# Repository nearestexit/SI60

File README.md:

# SI60

[QMK](https://github.com/qmk/qmk_firmware) Compatible Open Hardware GH60-compatible USB-C PCBs designed for use with [Hi-Tek 725 "Space Invaders" Switches](https://wiki.vintkeys.ca/NMB/Switches) in a variety of layouts, including variants of NMB keyboards with and without stepped caps.

## Overview
The main features of this project are:
 - Support for nearly every possible 60% set of caps you could use, including all NMB RT101+ keyboards in ANSI and ISO, with stepped and unstepped caps, Erase-Eaze, and ADDS/Televideo ANSI layouts.
 - Future-proof STM32F072CBT6 MCU
 - Design optimized for hand-soldering, with no parts smaller than 0603, and an MCU that does not require an external crystal
 - Compatibility with the original GH60 footprint
 - Compatibility (theoretically) with the Bakeneko60 footprint
 
 **Important: The distance from the plate to PCB on Space Invaders switches is larger than that for MX switches. You must do your own research to confirm compatibility with whatever case you choose.
 Tray-mount cases are likely to work okay, but for top-mount keyboards, the pins may short out on the bottom of the case.
 I will update this page when compatibility with a certain case is confirmed, but other than that, I cannot answer questions like "is X keyboard with this PCB"**

Production files are included for production at [JLCPCB](https://jlcpcb.com/).

## Supported layouts
 - Stepped and unstepped ISO, ANSI, BAE
 - Televideo ANSI bottom row
 - ADDS ANSI bottom row

**Please note: compatibility for the more obscure layouts is untested.**

## Configuration options
 - To fit in a GH60 case, the JST ought to be depopulated.
 - To fit in a Bakeneko60 case, the USB-C ought to be depopulated.

## JLCPCB Ordering Information
1. On jlcpcb.com, click "order now" and "add gerber file"
2. Navigate to the directory with the gerber.zip - for example, SI60\jlcpcb\production_files
3. Wait for the gerber to upload.
4. Select the number of PCBs you wish to build.
5. Make sure PCB thickness is set to 1.6mm.
6. Make sure Via covering is set to "tented".
7. Make sure Min via hole size/diameter is set to "0.3mm"
8. Turn the "PCB Assembly" option on
9. Make sure PCBA type is set to "Economic"
10. For "Assembly side", if you are ordering the daughterboard select "top side", otherwise select "bottom side"
11. Click "next", and then "next" again
12. Click "Add BOM File" and select the BOM csv - for example, BOM-SI60.csv
13. Click "Add CPL File" and select the CPL csv - for example, CPL-SI60.csv
14. Click "Process BOM and CPL"
15. Make sure all parts are in stock - if any are not in stock, you will need to find replacements
16. Decide whether you want the USB-C soldered or the JST soldered, and uncheck the box next to the one you don't want
17. **IMPORTANT:** Click "Bottom" to view the bottom side of the PCB, and begin inspecting the component placements. You **WILL** need to correct some component rotations. If you are not sure at this step, do not continue!
18. Click "next" and finish checking out.

## Firmware
- [Vial-QMK](https://get.vial.today/) .uf2 files are provided in the firmware folder.
- To put the keyboard into bootloader mode to flash the firmware:
1. Open QMK toolbox, select the firmware file, and check the box for "auto flash"
2. Unplug the USB cable
3. Short the 3v3 and BOOT0 pins with a pair of tweezers
4. Plug the USB cable in
5. Stop shorting the BOOT pins.
- The STM32 will then be recognized by QMK toolbox, and it will load the firmware.
- You may need to reconnect the keyboard after flashing.
- Once you have flashed the firmware, you can change the keymap from [vial.rocks](https://vial.rocks)

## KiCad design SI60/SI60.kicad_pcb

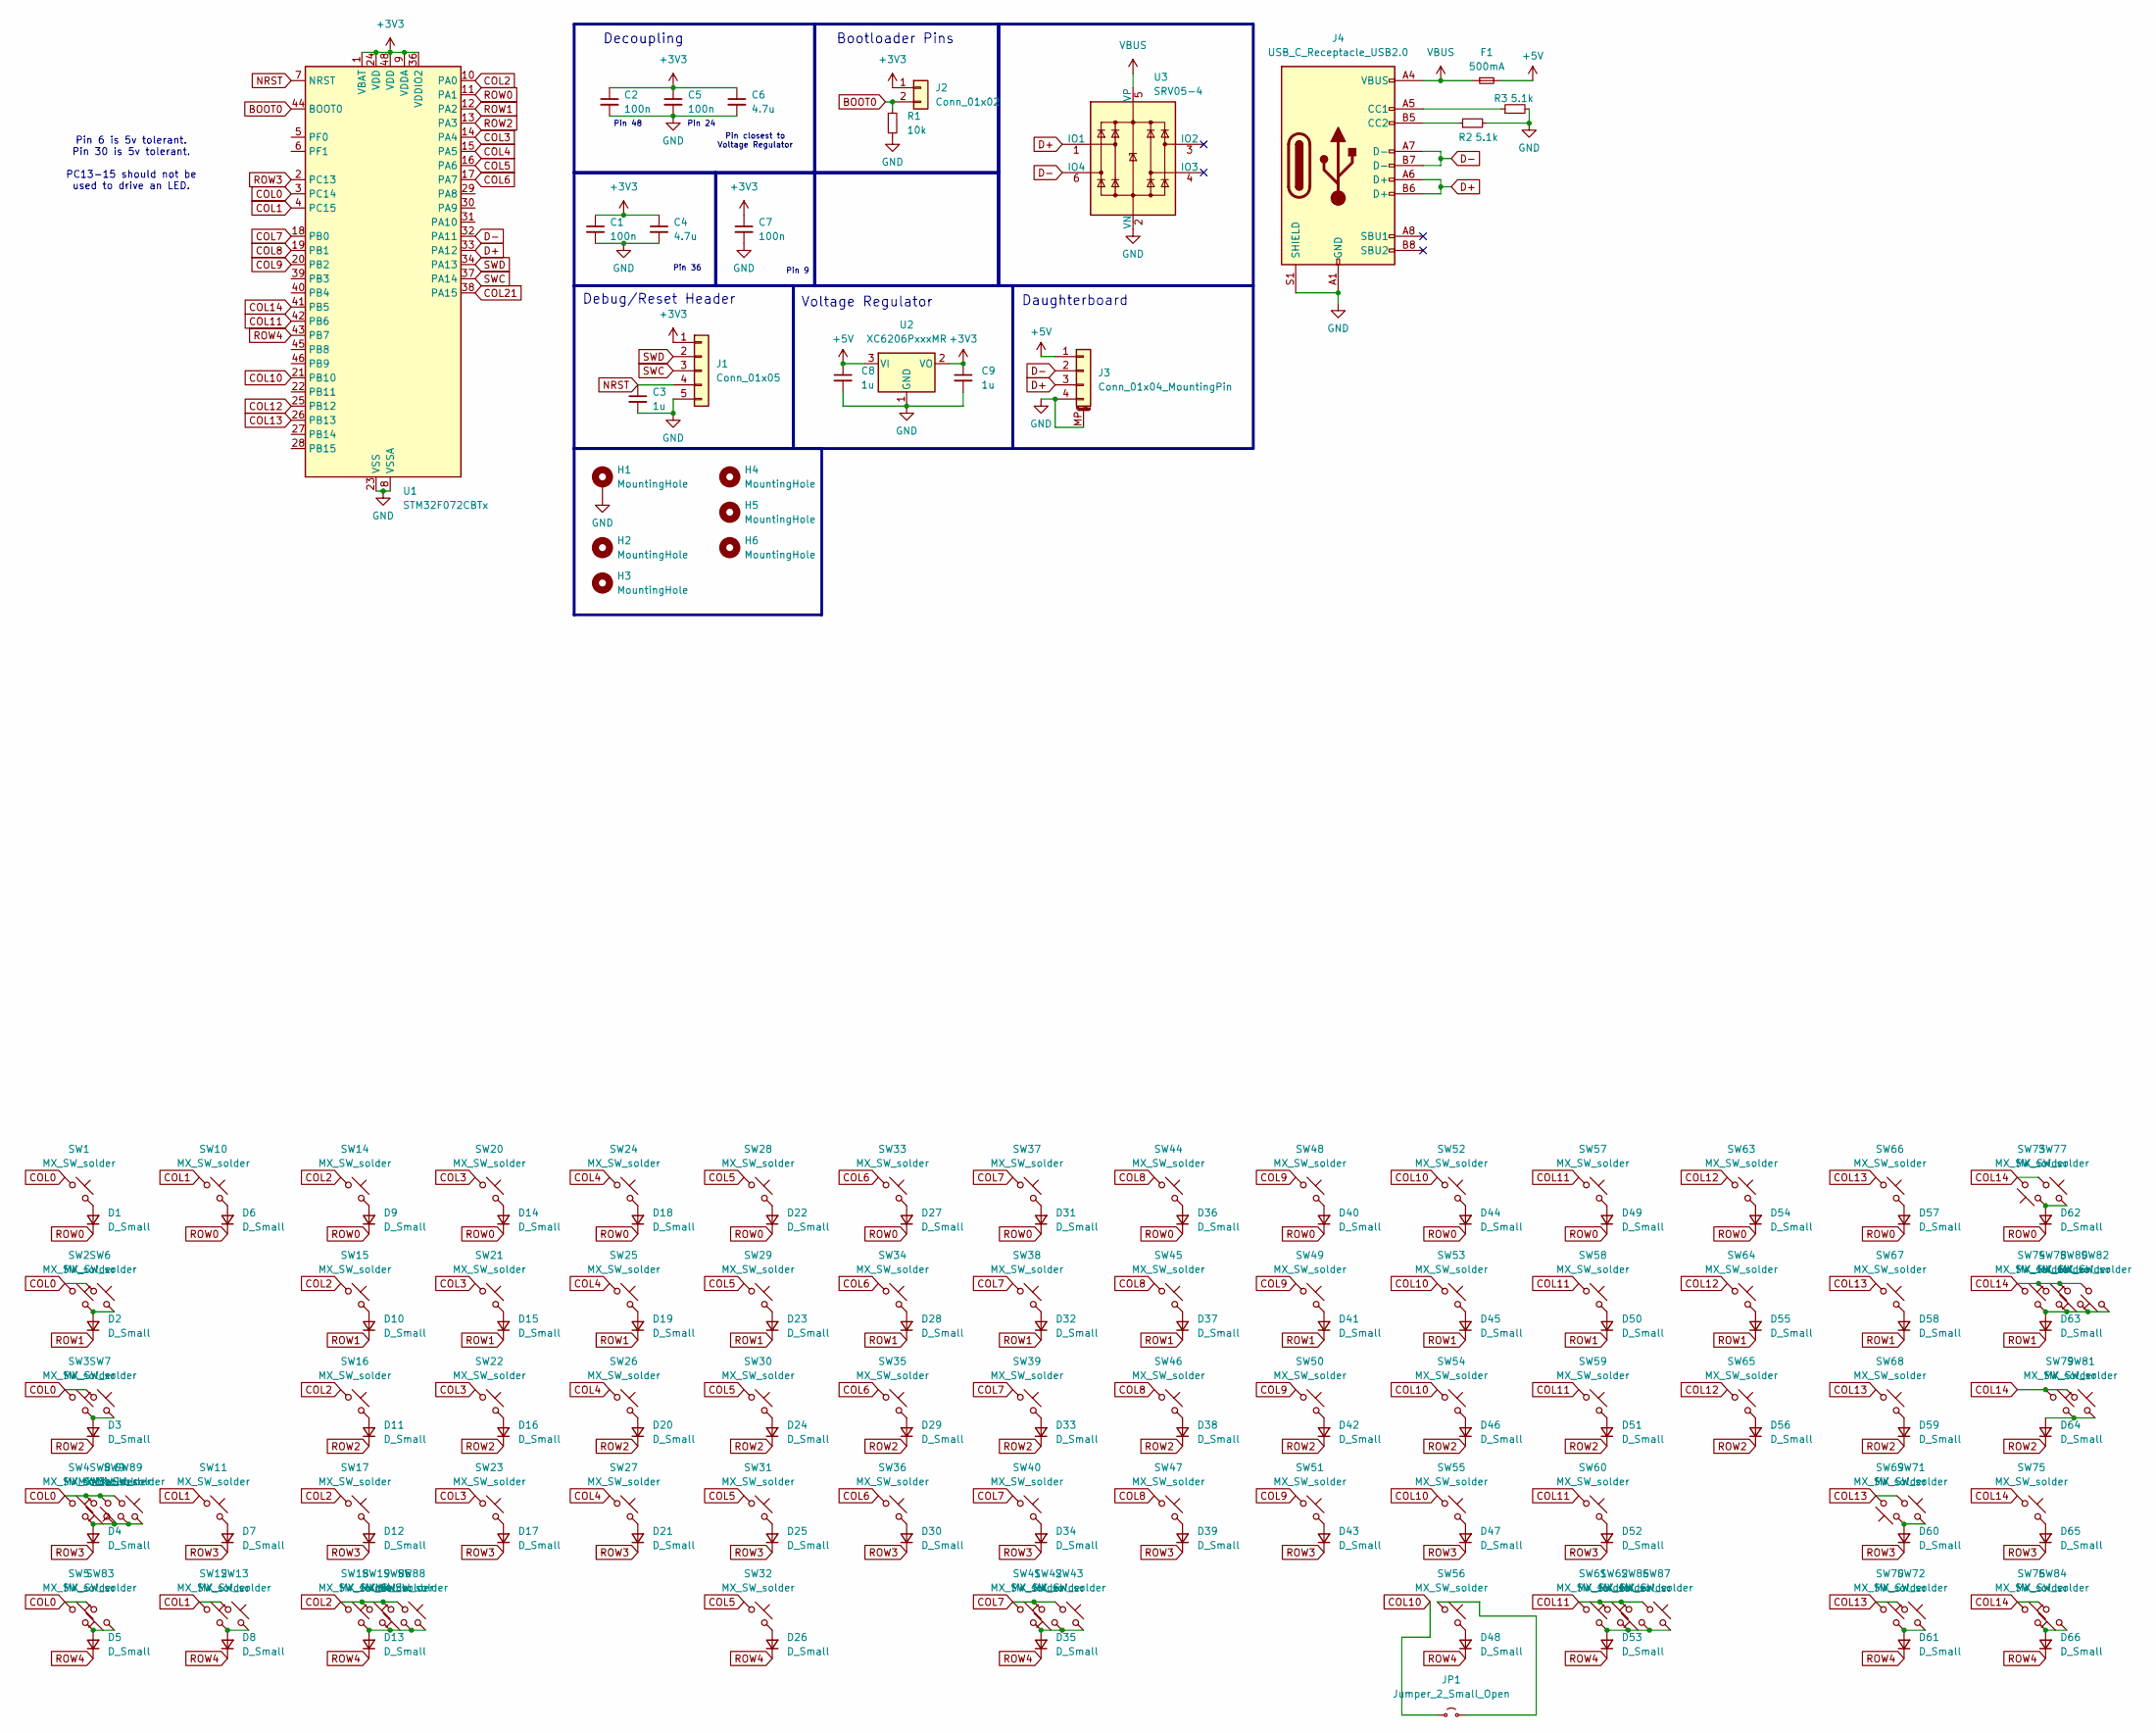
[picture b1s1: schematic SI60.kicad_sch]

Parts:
C1, C2, C5, C7: 100n; C_0603_1608Metric
C3, C8, C9: 1u; C_0805_2012Metric
C4, C6: 4.7u; C_0603_1608Metric
D1, D2, D3, D4, D5, D6, D7, D8, D9, D10, D11, D12, D13, D14, D15, D16, D17, D18, D19, D20, D21, D22, D23, D24, D25, D26, D27, D28, D29, D30, D31, D32, D33, D34, D35, D36, D37, D38, D39, D40, D41, D42, D43, D44, D45, D46, D47, D48, D49, D50, D51, D52, D53, D54, D55, D56, D57, D58, D59, D60, D61, D62, D63, D64, D65, D66: D_Small; D_SOD-123
F1: 500mA; Fuse_1206_3216Metric
H1: MountingHole; GH60_Standoff_Hole
H2, H3, H4: MountingHole; GH60_Standoff_Slot
H5, H6: MountingHole; GH60_Standoff_Slot_Edge
J1: Conn_01x05; PinHeader_1x05_P2.54mm_DEBUG
J2: Conn_01x02; PinHeader_1x02_P2.54mm_BOOT
J3: Conn_01x04_MountingPin; JST_SH_SM04B-SRSS-TB_1x04-1MP_P1.00mm_Horizontal
J4: USB_C_Receptacle_USB2.0; USB_C_Receptacle_HRO_TYPE-C-31-M-12
JP1: Jumper_2_Small_Open; SolderJumper-2_P1.3mm_Open_RoundedPad1.0x1.5mm
R1: 10k; R_0805_2012Metric
R2, R3: 5.1k; R_0603_1608Metric
SW1, SW2, SW3, SW4, SW5, SW6, SW7, SW8, SW10, SW12, SW13, SW15, SW16, SW17, SW19, SW20, SW21, SW22, SW23, SW24, SW25, SW26, SW27, SW28, SW29, SW30, SW31, SW32, SW33, SW34, SW35, SW36, SW37, SW38, SW39, SW40, SW41, SW42, SW43, SW44, SW45, SW46, SW47, SW48, SW49, SW50, SW51, SW52, SW53, SW54, SW55, SW56, SW57, SW58, SW59, SW60, SW62, SW63, SW64, SW65, SW67, SW69, SW70, SW71, SW72, SW73, SW74, SW75, SW76, SW78, SW79, SW83, SW84, SW85, SW86, SW89: MX_SW_solder; SW_HiTek725_1u
SW9, SW61, SW66, SW68, SW88: MX_SW_solder; SW_HiTek725_1u_OvalRight
SW11, SW18, SW77, SW81, SW87: MX_SW_solder; SW_HiTek725_1u_OvalLeft
SW14: MX_SW_solder; SW_HiTek725_1u_JST
SW80: MX_SW_solder; SW_HiTek725_BAE
SW82: MX_SW_solder; SW_HiTek725_ISO
U1: STM32F072CBTx; LQFP-48_7x7mm_P0.5mm
U2: XC6206PxxxMR; SOT-23-3
U3: SRV05-4; SOT-23-6-routable

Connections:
+3V3: C1.1, C2.1, C4.1, C5.1, C6.1, C7.1, C9.1, J1.1, J2.1, U1.1 (VBAT), U1.9 (VDDA), U1.24 (VDD), U1.36 (VDDIO2), U1.48 (VDD), U2.2 (VO)
+5V: C8.1, F1.2, J3.1, U2.3 (VI)
BOOT0: J2.2, R1.1, U1.44 (BOOT0)
COL0: SW1.1, SW2.1, SW3.1, SW4.1, SW5.1, SW6.1, SW7.1, SW8.2, SW9.2, SW83.2, SW89.1, U1.3 (PC14)
COL1: SW10.1, SW11.1, SW12.1, SW13.1, U1.4 (PC15)
COL2: SW14.1, SW15.1, SW16.1, SW17.1, SW18.1, SW19.1, SW85.2, SW88.1, U1.10 (PA0)
COL3: SW20.1, SW21.1, SW22.1, SW23.1, U1.14 (PA4)
COL4: SW24.1, SW25.1, SW26.1, SW27.1, U1.15 (PA5)
COL5: SW28.1, SW29.1, SW30.1, SW31.1, SW32.1, U1.16 (PA6)
COL6: SW33.1, SW34.1, SW35.1, SW36.1, U1.17 (PA7)
COL7: SW37.1, SW38.1, SW39.1, SW40.1, SW41.1, SW42.2, SW43.1, U1.18 (PB0)
COL8: SW44.1, SW45.1, SW46.1, SW47.1, U1.19 (PB1)
COL9: SW48.1, SW49.1, SW50.1, SW51.1, U1.20 (PB2)
COL10: JP1.1 (A), SW52.1, SW53.1, SW54.1, SW55.1, U1.21 (PB10)
COL11: SW57.1, SW58.1, SW59.1, SW60.1, SW61.1, SW62.1, SW86.2, SW87.1, U1.42 (PB6)
COL12: SW63.1, SW64.1, SW65.1, U1.25 (PB12)
COL13: SW66.1, SW67.1, SW68.1, SW69.2, SW70.1, SW71.1, SW72.1, U1.26 (PB13)
COL14: SW73.2, SW74.1, SW75.1, SW76.1, SW77.1, SW78.1, SW79.1, SW80.2, SW81.1, SW82.2, SW84.2, U1.41 (PB5)
COL21: U1.38 (PA15)
D+: J3.3, J4.A6 (D+), J4.B6 (D+), U1.33 (PA12), U3.1 (IO1)
D-: J3.2, J4.A7 (D-), J4.B7 (D-), U1.32 (PA11), U3.6 (IO4)
GND: C1.2, C2.2, C3.2, C4.2, C5.2, C6.2, C7.2, C8.2, C9.2, H1.1, J1.5, J3.4, J3.MP (MountPin), J4.A1 (GND), J4.A12 (GND), J4.B1 (GND), J4.B12 (GND), J4.S1 (SHIELD), R1.2, R2.2, R3.2, U1.8 (VSSA), U1.23 (VSS), U1.35 (VSS), U1.47 (VSS), U2.1 (GND), U3.2 (VN)
NRST: C3.1, J1.4, U1.7 (NRST)
unnamed: D1.2 (A), SW1.2
unnamed: D2.2 (A), SW2.2, SW6.2
unnamed: D3.2 (A), SW3.2, SW7.2
unnamed: D4.2 (A), SW4.2, SW8.1, SW9.1, SW89.2
unnamed: D5.2 (A), SW5.2, SW83.1
unnamed: D6.2 (A), SW10.2
unnamed: D7.2 (A), SW11.2
unnamed: D8.2 (A), SW12.2, SW13.2
unnamed: D9.2 (A), SW14.2
unnamed: D10.2 (A), SW15.2
unnamed: D11.2 (A), SW16.2
unnamed: D12.2 (A), SW17.2
unnamed: D13.2 (A), SW18.2, SW19.2, SW85.1, SW88.2
unnamed: D14.2 (A), SW20.2
unnamed: D15.2 (A), SW21.2
unnamed: D16.2 (A), SW22.2
unnamed: D17.2 (A), SW23.2
unnamed: D18.2 (A), SW24.2
unnamed: D19.2 (A), SW25.2
unnamed: D20.2 (A), SW26.2
unnamed: D21.2 (A), SW27.2
unnamed: D22.2 (A), SW28.2
unnamed: D23.2 (A), SW29.2
unnamed: D24.2 (A), SW30.2
unnamed: D25.2 (A), SW31.2
unnamed: D26.2 (A), SW32.2
unnamed: D27.2 (A), SW33.2
unnamed: D28.2 (A), SW34.2
unnamed: D29.2 (A), SW35.2
unnamed: D30.2 (A), SW36.2
unnamed: D31.2 (A), SW37.2
unnamed: D32.2 (A), SW38.2
unnamed: D33.2 (A), SW39.2
unnamed: D34.2 (A), SW40.2
unnamed: D35.2 (A), SW41.2, SW42.1, SW43.2
unnamed: D36.2 (A), SW44.2
unnamed: D37.2 (A), SW45.2
unnamed: D38.2 (A), SW46.2
unnamed: D39.2 (A), SW47.2
unnamed: D40.2 (A), SW48.2
unnamed: D41.2 (A), SW49.2
unnamed: D42.2 (A), SW50.2
unnamed: D43.2 (A), SW51.2
unnamed: D44.2 (A), SW52.2
unnamed: D45.2 (A), SW53.2
unnamed: D46.2 (A), SW54.2
unnamed: D47.2 (A), SW55.2
unnamed: D48.2 (A), SW56.2
unnamed: D49.2 (A), SW57.2
unnamed: D50.2 (A), SW58.2
unnamed: D51.2 (A), SW59.2
unnamed: D52.2 (A), SW60.2
unnamed: D53.2 (A), SW61.2, SW62.2, SW86.1, SW87.2
unnamed: D54.2 (A), SW63.2
unnamed: D55.2 (A), SW64.2
unnamed: D56.2 (A), SW65.2
unnamed: D57.2 (A), SW66.2
unnamed: D58.2 (A), SW67.2
unnamed: D59.2 (A), SW68.2
unnamed: D60.2 (A), SW69.1, SW71.2
unnamed: D61.2 (A), SW70.2, SW72.2
unnamed: D62.2 (A), SW73.1, SW77.2
unnamed: D63.2 (A), SW74.2, SW78.2, SW80.1, SW82.1
unnamed: D64.2 (A), SW79.2, SW81.2
unnamed: D65.2 (A), SW75.2
unnamed: D66.2 (A), SW76.2, SW84.1
unnamed: J4.A5 (CC1), R3.1
unnamed: J4.B5 (CC2), R2.1
unnamed: JP1.2 (B), SW56.1
ROW0: D1.1 (K), D6.1 (K), D9.1 (K), D14.1 (K), D18.1 (K), D22.1 (K), D27.1 (K), D31.1 (K), D36.1 (K), D40.1 (K), D44.1 (K), D49.1 (K), D54.1 (K), D57.1 (K), D62.1 (K), U1.11 (PA1)
ROW1: D2.1 (K), D10.1 (K), D15.1 (K), D19.1 (K), D23.1 (K), D28.1 (K), D32.1 (K), D37.1 (K), D41.1 (K), D45.1 (K), D50.1 (K), D55.1 (K), D58.1 (K), D63.1 (K), U1.12 (PA2)
ROW2: D3.1 (K), D11.1 (K), D16.1 (K), D20.1 (K), D24.1 (K), D29.1 (K), D33.1 (K), D38.1 (K), D42.1 (K), D46.1 (K), D51.1 (K), D56.1 (K), D59.1 (K), D64.1 (K), U1.13 (PA3)
ROW3: D4.1 (K), D7.1 (K), D12.1 (K), D17.1 (K), D21.1 (K), D25.1 (K), D30.1 (K), D34.1 (K), D39.1 (K), D43.1 (K), D47.1 (K), D52.1 (K), D60.1 (K), D65.1 (K), U1.2 (PC13)
ROW4: D5.1 (K), D8.1 (K), D13.1 (K), D26.1 (K), D35.1 (K), D48.1 (K), D53.1 (K), D61.1 (K), D66.1 (K), U1.43 (PB7)
SWC: J1.3, U1.37 (PA14)
SWD: J1.2, U1.34 (PA13)
VBUS: F1.1, J4.A4 (VBUS), J4.A9 (VBUS), J4.B4 (VBUS), J4.B9 (VBUS), U3.5 (VP)

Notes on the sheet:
Pin closest to Voltage Regulator
Pin 6 is 5v tolerant. Pin 30 is 5v tolerant. PC13-15 should not be used to drive an LED.
Debug/Reset Header
Daughterboard
Pin 48
Pin 36
Pin 24
Pin 9
Decoupling
Bootloader Pins
Voltage Regulator

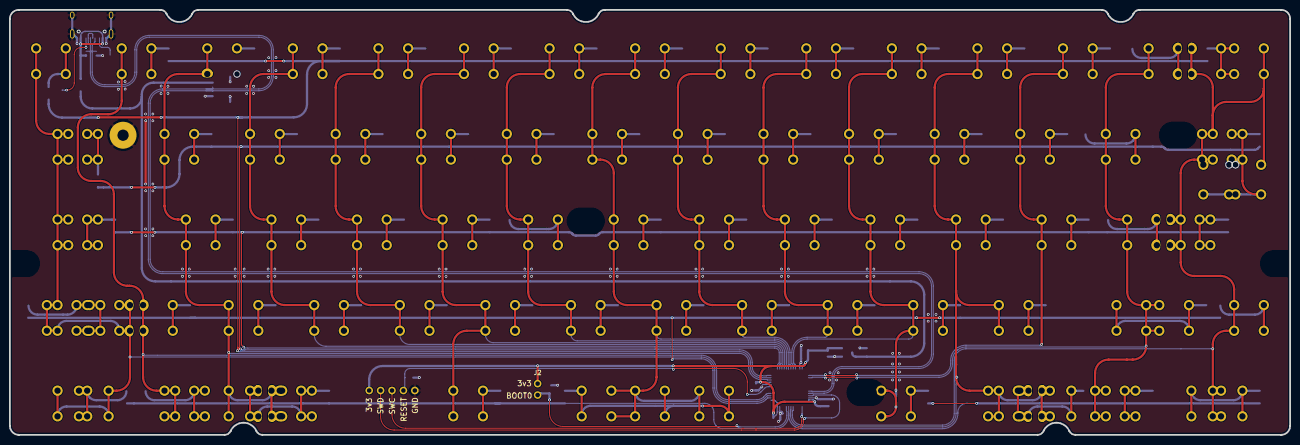
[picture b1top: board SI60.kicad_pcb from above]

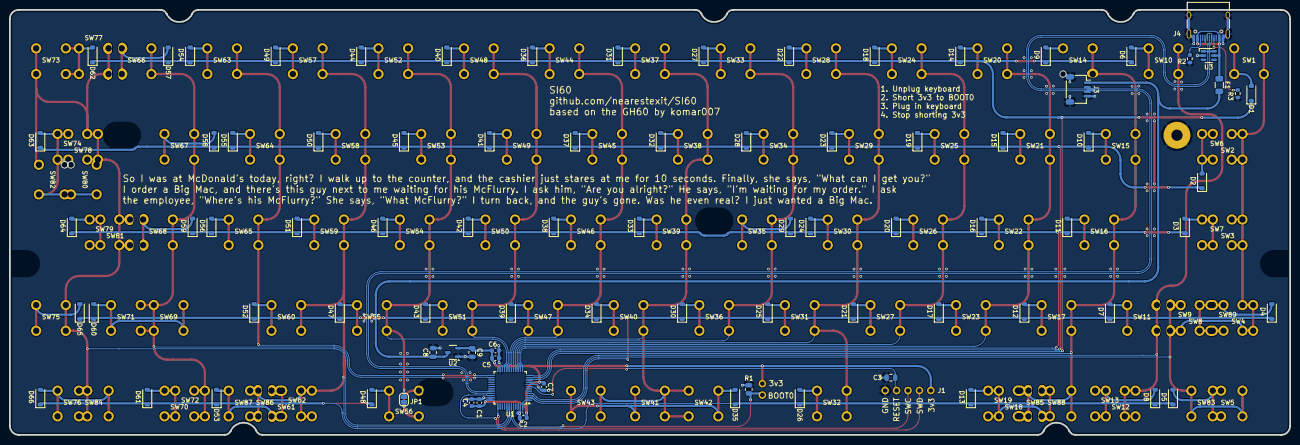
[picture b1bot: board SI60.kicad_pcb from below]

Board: 2 copper layers, 285.0 x 94.6 mm, 182 parts (85 on the bottom side), 99 nets.

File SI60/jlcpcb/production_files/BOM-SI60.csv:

Comment,Designator,Footprint,LCSC,Quantity
100n,"C1,C2,C5,C7",C_0603_1608Metric,C14663,4
Conn_01x04_MountingPin,J3,JST_SH_SM04B-SRSS-TB_1x04-1MP_P1.00mm_Horizontal,C160404,1
USB_C_Receptacle_USB2.0,J4,USB_C_Receptacle_HRO_TYPE-C-31-M-12,C165948,1
10k,R1,R_0805_2012Metric,C17414,1
4.7u,"C4,C6",C_0603_1608Metric,C19666,2
5.1k,"R2,R3",R_0603_1608Metric,C23186,2
1u,"C3,C8,C9",C_0805_2012Metric,C28323,3
XC6206PxxxMR,U2,SOT-23-3,C5446,1
500mA,F1,Fuse_1206_3216Metric,C70076,1
D_Small,"D1,D10,D11,D12,D13,D14,D15,D16,D17,D18,D19,D2,D20,D21,D22,D23,D24,D25,D26,D27,D28,D29,D3,D30,D31,D32,D33,D34,D35,D36,D37,D38,D39,D4,D40,D41,D42,D43,D44,D45,D46,D47,D48,D49,D5,D50,D51,D52,D53,D54,D55,D56,D57,D58,D59,D6,D60,D61,D62,D63,D64,D65,D66,D7,D8,D9",D_SOD-123,C81598,66
STM32F072CBTx,U1,LQFP-48_7x7mm_P0.5mm,C81720,1
SRV05-4,U3,SOT-23-6-routable,C85364,1

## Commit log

2025-06-01 Update Production Files
